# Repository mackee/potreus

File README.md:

# Potreus Keyboard

Potreus Keyboard is a row staggered mechanical keyboard optimized 60% caces. Inspired by [Atreus Keyboard](https://gitlab.com/technomancy/atreus).

## Images

## License

Copyright © 2021 mackee

Released under the [CC BY-SA 4.0](https://creativecommons.org/licenses/by-sa/4.0/).

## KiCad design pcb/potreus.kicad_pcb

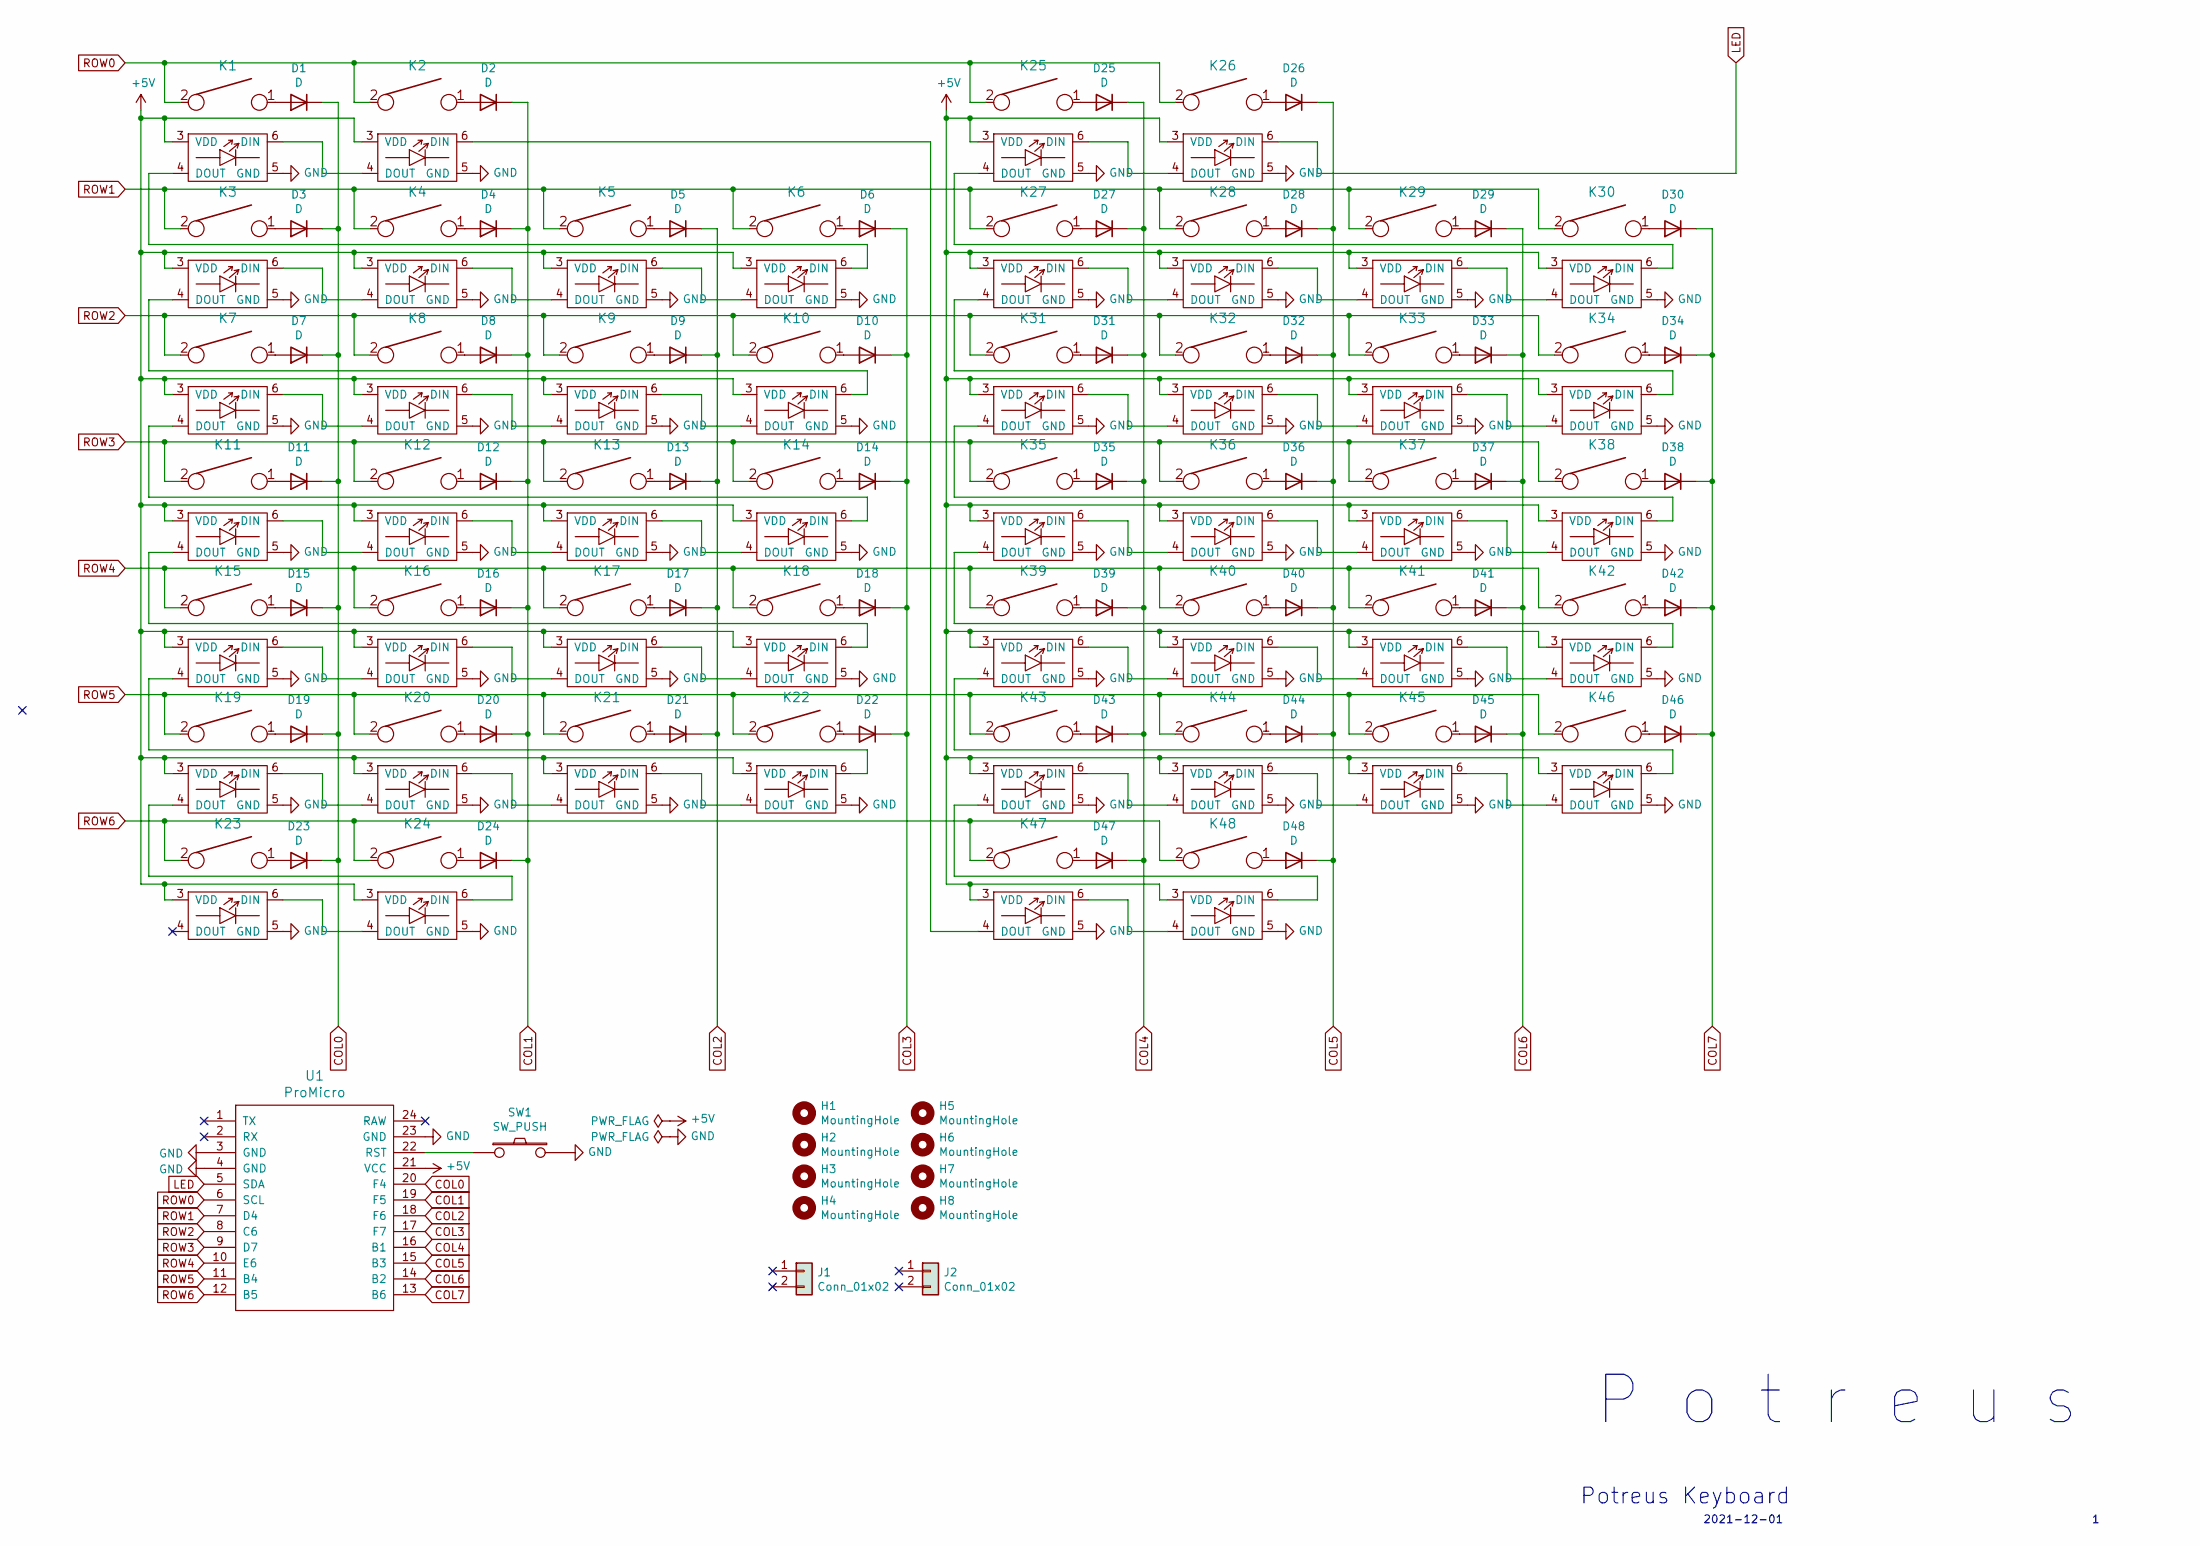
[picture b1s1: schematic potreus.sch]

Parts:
D1, D2, D3, D4, D5, D6, D7, D8, D9, D10, D11, D12, D13, D14, D15, D16, D17, D18, D19, D20, D21, D22, D23, D24, D25, D26, D27, D28, D29, D30, D31, D32, D33, D34, D35, D36, D37, D38, D39, D40, D41, D42, D43, D44, D45, D46, D47, D48: D; Diode_SMD
H1, H2, H3, H4: MountingHole; Poker_oval_hole
H5, H6, H7, H8: MountingHole; M2_Hole_TH
J1, J2: Conn_01x02; Pin_Header_Straight_1x02_Pitch2.54mm
K1, K2, K3, K4, K5, K6, K7, K8, K9, K10, K11, K12, K13, K14, K15, K16, K17, K18, K19, K20, K21, K22, K23, K24, K25, K26, K27, K28, K29, K30, K31, K32, K33, K34, K35, K36, K37, K38, K39, K40, K41, K42, K43, K44, K45, K46, K47, K48: KEYSW_SK6812MINI-E; Kailh_socket_with_SK6812MINI-E
SW1: SW_PUSH; tactswitch-2lead-6mm
U1: ProMicro

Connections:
+5V: K1.3 (VDD), K2.3 (VDD), K3.3 (VDD), K4.3 (VDD), K5.3 (VDD), K6.3 (VDD), K7.3 (VDD), K8.3 (VDD), K9.3 (VDD), K10.3 (VDD), K11.3 (VDD), K12.3 (VDD), K13.3 (VDD), K14.3 (VDD), K15.3 (VDD), K16.3 (VDD), K17.3 (VDD), K18.3 (VDD), K19.3 (VDD), K20.3 (VDD), K21.3 (VDD), K22.3 (VDD), K23.3 (VDD), K24.3 (VDD), K25.3 (VDD), K26.3 (VDD), K27.3 (VDD), K28.3 (VDD), K29.3 (VDD), K30.3 (VDD), K31.3 (VDD), K32.3 (VDD), K33.3 (VDD), K34.3 (VDD), K35.3 (VDD), K36.3 (VDD), K37.3 (VDD), K38.3 (VDD), K39.3 (VDD), K40.3 (VDD), K41.3 (VDD), K42.3 (VDD), K43.3 (VDD), K44.3 (VDD), K45.3 (VDD), K46.3 (VDD), K47.3 (VDD), K48.3 (VDD), U1.21 (VCC)
COL0: D1.1 (K), D3.1 (K), D7.1 (K), D11.1 (K), D15.1 (K), D19.1 (K), D23.1 (K), U1.20 (F4)
COL1: D2.1 (K), D4.1 (K), D8.1 (K), D12.1 (K), D16.1 (K), D20.1 (K), D24.1 (K), U1.19 (F5)
COL2: D5.1 (K), D9.1 (K), D13.1 (K), D17.1 (K), D21.1 (K), U1.18 (F6)
COL3: D6.1 (K), D10.1 (K), D14.1 (K), D18.1 (K), D22.1 (K), U1.17 (F7)
COL4: D25.1 (K), D27.1 (K), D31.1 (K), D35.1 (K), D39.1 (K), D43.1 (K), D47.1 (K), U1.16 (B1)
COL5: D26.1 (K), D28.1 (K), D32.1 (K), D36.1 (K), D40.1 (K), D44.1 (K), D48.1 (K), U1.15 (B3)
COL6: D29.1 (K), D33.1 (K), D37.1 (K), D41.1 (K), D45.1 (K), U1.14 (B2)
COL7: D30.1 (K), D34.1 (K), D38.1 (K), D42.1 (K), D46.1 (K), U1.13 (B6)
GND: K1.5 (GND), K2.5 (GND), K3.5 (GND), K4.5 (GND), K5.5 (GND), K6.5 (GND), K7.5 (GND), K8.5 (GND), K9.5 (GND), K10.5 (GND), K11.5 (GND), K12.5 (GND), K13.5 (GND), K14.5 (GND), K15.5 (GND), K16.5 (GND), K17.5 (GND), K18.5 (GND), K19.5 (GND), K20.5 (GND), K21.5 (GND), K22.5 (GND), K23.5 (GND), K24.5 (GND), K25.5 (GND), K26.5 (GND), K27.5 (GND), K28.5 (GND), K29.5 (GND), K30.5 (GND), K31.5 (GND), K32.5 (GND), K33.5 (GND), K34.5 (GND), K35.5 (GND), K36.5 (GND), K37.5 (GND), K38.5 (GND), K39.5 (GND), K40.5 (GND), K41.5 (GND), K42.5 (GND), K43.5 (GND), K44.5 (GND), K45.5 (GND), K46.5 (GND), K47.5 (GND), K48.5 (GND), SW1.2, U1.3 (GND), U1.4 (GND), U1.23 (GND)
LED: K26.6 (DIN), U1.5 (SDA)
unnamed: D1.2 (A), K1.1
unnamed: D2.2 (A), K2.1
unnamed: D3.2 (A), K3.1
unnamed: D4.2 (A), K4.1
unnamed: D5.2 (A), K5.1
unnamed: D6.2 (A), K6.1
unnamed: D7.2 (A), K7.1
unnamed: D8.2 (A), K8.1
unnamed: D9.2 (A), K9.1
unnamed: D10.2 (A), K10.1
unnamed: D11.2 (A), K11.1
unnamed: D12.2 (A), K12.1
unnamed: D13.2 (A), K13.1
unnamed: D14.2 (A), K14.1
unnamed: D15.2 (A), K15.1
unnamed: D16.2 (A), K16.1
unnamed: D17.2 (A), K17.1
unnamed: D18.2 (A), K18.1
unnamed: D19.2 (A), K19.1
unnamed: D20.2 (A), K20.1
unnamed: D21.2 (A), K21.1
unnamed: D22.2 (A), K22.1
unnamed: D23.2 (A), K23.1
unnamed: D24.2 (A), K24.1
unnamed: D25.2 (A), K25.1
unnamed: D26.2 (A), K26.1
unnamed: D27.2 (A), K27.1
unnamed: D28.2 (A), K28.1
unnamed: D29.2 (A), K29.1
unnamed: D30.2 (A), K30.1
unnamed: D31.2 (A), K31.1
unnamed: D32.2 (A), K32.1
unnamed: D33.2 (A), K33.1
unnamed: D34.2 (A), K34.1
unnamed: D35.2 (A), K35.1
unnamed: D36.2 (A), K36.1
unnamed: D37.2 (A), K37.1
unnamed: D38.2 (A), K38.1
unnamed: D39.2 (A), K39.1
unnamed: D40.2 (A), K40.1
unnamed: D41.2 (A), K41.1
unnamed: D42.2 (A), K42.1
unnamed: D43.2 (A), K43.1
unnamed: D44.2 (A), K44.1
unnamed: D45.2 (A), K45.1
unnamed: D46.2 (A), K46.1
unnamed: D47.2 (A), K47.1
unnamed: D48.2 (A), K48.1
unnamed: K1.4 (DOUT), K6.6 (DIN)
unnamed: K1.6 (DIN), K2.4 (DOUT)
unnamed: K2.6 (DIN), K47.4 (DOUT)
unnamed: K3.6 (DIN), K4.4 (DOUT)
unnamed: K4.6 (DIN), K5.4 (DOUT)
unnamed: K5.6 (DIN), K6.4 (DOUT)
unnamed: K7.6 (DIN), K8.4 (DOUT)
unnamed: K8.6 (DIN), K9.4 (DOUT)
unnamed: K9.6 (DIN), K10.4 (DOUT)
unnamed: K3.4 (DOUT), K10.6 (DIN)
unnamed: K11.4 (DOUT), K18.6 (DIN)
unnamed: K11.6 (DIN), K12.4 (DOUT)
unnamed: K12.6 (DIN), K13.4 (DOUT)
unnamed: K13.6 (DIN), K14.4 (DOUT)
unnamed: K7.4 (DOUT), K14.6 (DIN)
unnamed: K15.4 (DOUT), K22.6 (DIN)
unnamed: K15.6 (DIN), K16.4 (DOUT)
unnamed: K16.6 (DIN), K17.4 (DOUT)
unnamed: K17.6 (DIN), K18.4 (DOUT)
unnamed: K19.4 (DOUT), K24.6 (DIN)
unnamed: K19.6 (DIN), K20.4 (DOUT)
unnamed: K20.6 (DIN), K21.4 (DOUT)
unnamed: K21.6 (DIN), K22.4 (DOUT)
unnamed: K23.6 (DIN), K24.4 (DOUT)
unnamed: K25.4 (DOUT), K30.6 (DIN)
unnamed: K25.6 (DIN), K26.4 (DOUT)
unnamed: K27.4 (DOUT), K34.6 (DIN)
unnamed: K27.6 (DIN), K28.4 (DOUT)
unnamed: K28.6 (DIN), K29.4 (DOUT)
unnamed: K29.6 (DIN), K30.4 (DOUT)
unnamed: K31.4 (DOUT), K38.6 (DIN)
unnamed: K31.6 (DIN), K32.4 (DOUT)
unnamed: K32.6 (DIN), K33.4 (DOUT)
unnamed: K33.6 (DIN), K34.4 (DOUT)
unnamed: K35.4 (DOUT), K42.6 (DIN)
unnamed: K35.6 (DIN), K36.4 (DOUT)
unnamed: K36.6 (DIN), K37.4 (DOUT)
unnamed: K37.6 (DIN), K38.4 (DOUT)
unnamed: K39.4 (DOUT), K46.6 (DIN)
unnamed: K39.6 (DIN), K40.4 (DOUT)
unnamed: K40.6 (DIN), K41.4 (DOUT)
unnamed: K41.6 (DIN), K42.4 (DOUT)
unnamed: K43.4 (DOUT), K48.6 (DIN)
unnamed: K43.6 (DIN), K44.4 (DOUT)
unnamed: K44.6 (DIN), K45.4 (DOUT)
unnamed: K45.6 (DIN), K46.4 (DOUT)
unnamed: K47.6 (DIN), K48.4 (DOUT)
unnamed: SW1.1, U1.22 (RST)
ROW0: K1.2, K2.2, K25.2, K26.2, U1.6 (SCL)
ROW1: K3.2, K4.2, K5.2, K6.2, K27.2, K28.2, K29.2, K30.2, U1.7 (D4)
ROW2: K7.2, K8.2, K9.2, K10.2, K31.2, K32.2, K33.2, K34.2, U1.8 (C6)
ROW3: K11.2, K12.2, K13.2, K14.2, K35.2, K36.2, K37.2, K38.2, U1.9 (D7)
ROW4: K15.2, K16.2, K17.2, K18.2, K39.2, K40.2, K41.2, K42.2, U1.10 (E6)
ROW5: K19.2, K20.2, K21.2, K22.2, K43.2, K44.2, K45.2, K46.2, U1.11 (B4)
ROW6: K23.2, K24.2, K47.2, K48.2, U1.12 (B5)

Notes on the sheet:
P o t r e u s
2021-12-01
Potreus Keyboard

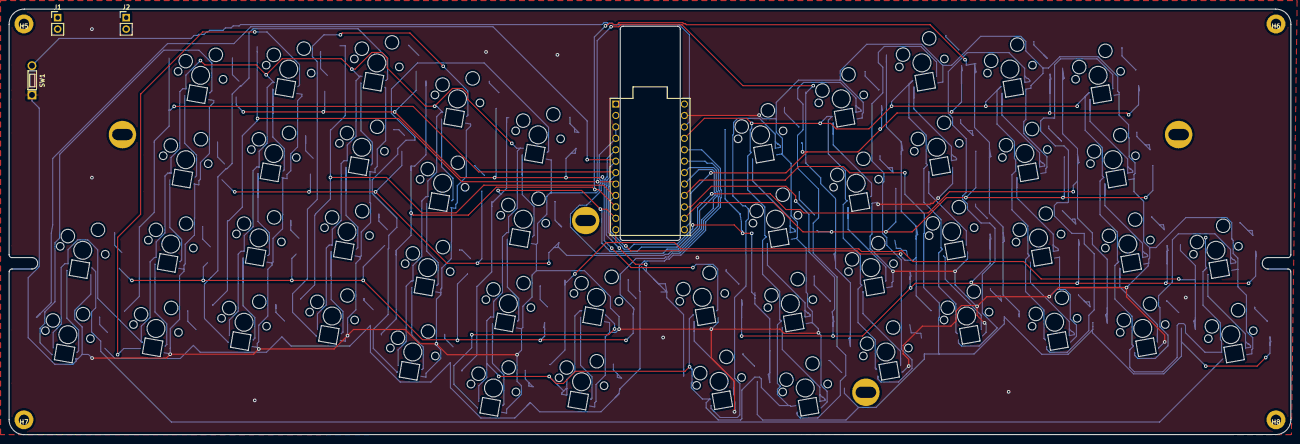
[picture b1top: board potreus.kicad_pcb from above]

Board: 2 copper layers, 284.9 x 94.5 mm, 108 parts (0 on the bottom side), 114 nets.

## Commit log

2021-12-29 add README
2021-12-29 fix readme
